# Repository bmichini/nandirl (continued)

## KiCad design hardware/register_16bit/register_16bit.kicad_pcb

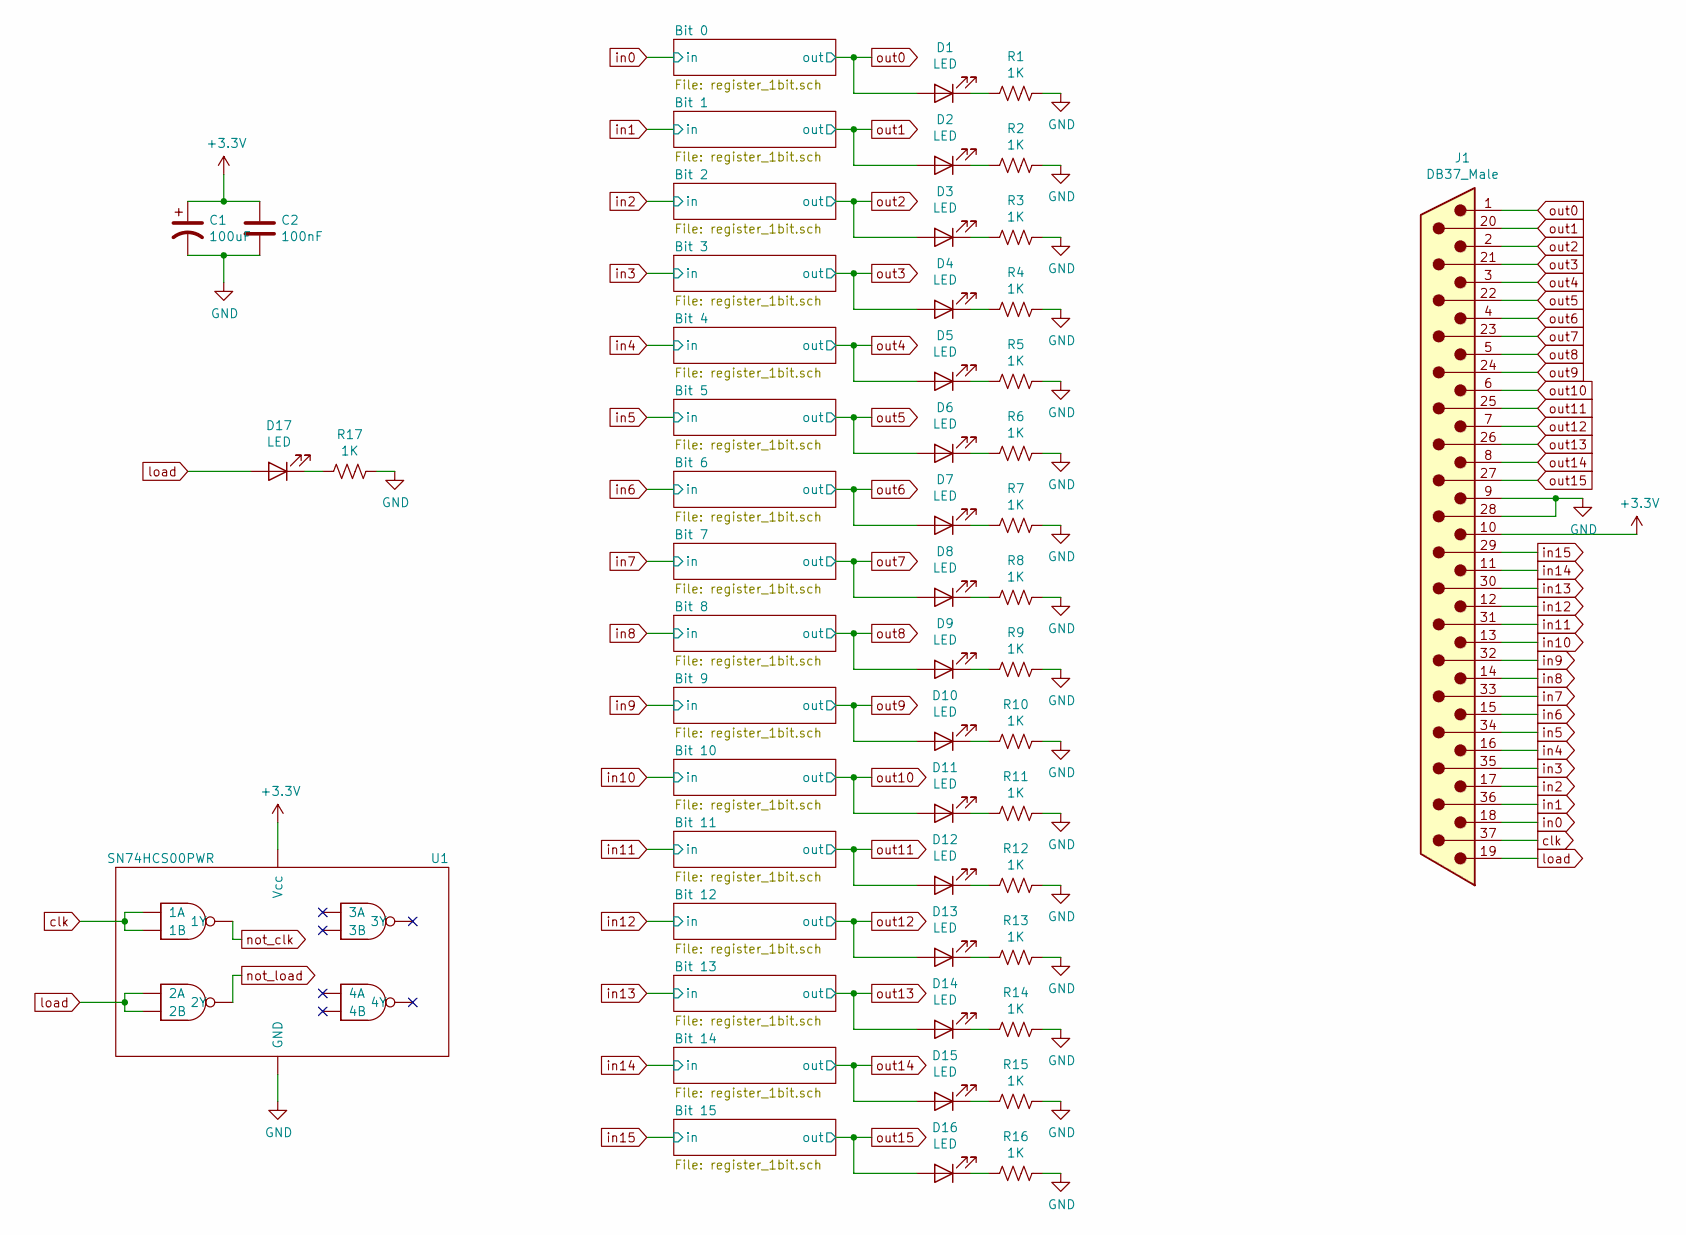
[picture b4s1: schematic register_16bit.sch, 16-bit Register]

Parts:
C1: 100uF; CP_Radial_D8.0mm_P2.50mm; Digikey PN P15797CT-ND
C2: 100nF; C_Disc_D5.0mm_W2.5mm_P5.00mm; Digikey PN BC5229CT-ND
D1, D2, D3, D4, D5, D6, D7, D8, D9, D10, D11, D12, D13, D14, D15, D16, D17: LED; LED_D5.0mm
J1: DB37_Male; DSUB-37_Male_Horizontal_P2.77x2.84mm_EdgePinOffset7.70mm_Ho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; Digikey PN AE10986-ND
R1, R2, R3, R4, R5, R6, R7, R8, R9, R10, R11, R12, R13, R14, R15, R16, R17: 1K; R_1206_3216Metric; Digikey PN P1.0KECT-ND
U1: SN74HCS00PWR; TSSOP-14_4.4x5mm_P0.65mm; Digikey PN 296-SN74HCS00PWRCT-ND

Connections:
+3V3: C1.1, C2.1, J1.10, U1.14 (Vcc); also elsewhere on the board
GND: C1.2, C2.2, J1.9, J1.28, R1.1, R2.1, R3.1, R4.1, R5.1, R6.1, R7.1, R8.1, R9.1, R10.1, R11.1, R12.1, R13.1, R14.1, R15.1, R16.1, R17.1, U1.7 (GND); also elsewhere on the board
unnamed: D1.1 (K), R1.2
unnamed: D2.1 (K), R2.2
unnamed: D3.1 (K), R3.2
unnamed: D4.1 (K), R4.2
unnamed: D5.1 (K), R5.2
unnamed: D6.1 (K), R6.2
unnamed: D7.1 (K), R7.2
unnamed: D8.1 (K), R8.2
unnamed: D9.1 (K), R9.2
unnamed: D10.1 (K), R10.2
unnamed: D11.1 (K), R11.2
unnamed: D12.1 (K), R12.2
unnamed: D13.1 (K), R13.2
unnamed: D14.1 (K), R14.2
unnamed: D15.1 (K), R15.2
unnamed: D16.1 (K), R16.2
unnamed: D17.1 (K), R17.2
clk: J1.37, U1.1 (1A), U1.2 (1B); also elsewhere on the board
in0: J1.18; also elsewhere on the board
in1: J1.36; also elsewhere on the board
in2: J1.17; also elsewhere on the board
in3: J1.35; also elsewhere on the board
in4: J1.16; also elsewhere on the board
in5: J1.34; also elsewhere on the board
in6: J1.15; also elsewhere on the board
in7: J1.33; also elsewhere on the board
in8: J1.14; also elsewhere on the board
in9: J1.32; also elsewhere on the board
in10: J1.13; also elsewhere on the board
in11: J1.31; also elsewhere on the board
in12: J1.12; also elsewhere on the board
in13: J1.30; also elsewhere on the board
in14: J1.11; also elsewhere on the board
in15: J1.29; also elsewhere on the board
load: D17.2 (A), J1.19, U1.4 (2A), U1.5 (2B); also elsewhere on the board
not_clk: U1.3 (1Y); also elsewhere on the board
not_load: U1.6 (2Y); also elsewhere on the board
out0: D1.2 (A), J1.1; also elsewhere on the board
out1: D2.2 (A), J1.20; also elsewhere on the board
out2: D3.2 (A), J1.2; also elsewhere on the board
out3: D4.2 (A), J1.21; also elsewhere on the board
out4: D5.2 (A), J1.3; also elsewhere on the board
out5: D6.2 (A), J1.22; also elsewhere on the board
out6: D7.2 (A), J1.4; also elsewhere on the board
out7: D8.2 (A), J1.23; also elsewhere on the board
out8: D9.2 (A), J1.5; also elsewhere on the board
out9: D10.2 (A), J1.24; also elsewhere on the board
out10: D11.2 (A), J1.6; also elsewhere on the board
out11: D12.2 (A), J1.25; also elsewhere on the board
out12: D13.2 (A), J1.7; also elsewhere on the board
out13: D14.2 (A), J1.26; also elsewhere on the board
out14: D15.2 (A), J1.8; also elsewhere on the board
out15: D16.2 (A), J1.27; also elsewhere on the board

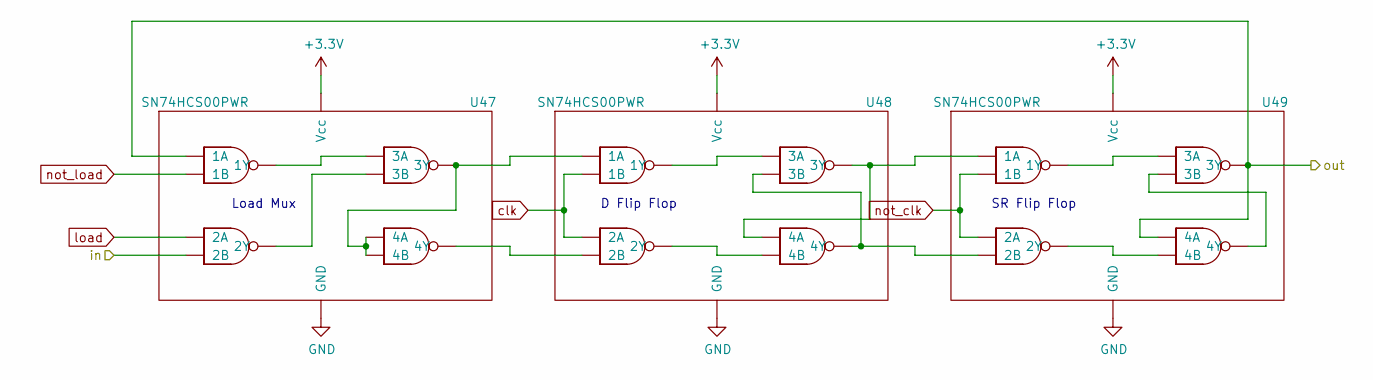
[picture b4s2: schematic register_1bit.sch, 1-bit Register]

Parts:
U47, U48, U49: SN74HCS00PWR; TSSOP-14_4.4x5mm_P0.65mm; Digikey PN 296-SN74HCS00PWRCT-ND

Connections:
+3V3: U47.14 (Vcc), U48.14 (Vcc), U49.14 (Vcc); also elsewhere on the board
GND: U47.7 (GND), U48.7 (GND), U49.7 (GND); also elsewhere on the board
unnamed: U47.3 (1Y), U47.9 (3A)
unnamed: U47.6 (2Y), U47.10 (3B)
unnamed: U47.11 (4Y), U48.5 (2B)
unnamed: U47.8 (3Y), U47.12 (4A), U47.13 (4B), U48.1 (1A)
unnamed: U48.3 (1Y), U48.9 (3A)
unnamed: U48.10 (3B), U48.11 (4Y), U49.5 (2B)
unnamed: U48.8 (3Y), U48.12 (4A), U49.1 (1A)
unnamed: U48.6 (2Y), U48.13 (4B)
unnamed: U49.3 (1Y), U49.9 (3A)
unnamed: U49.10 (3B), U49.11 (4Y)
unnamed: U49.6 (2Y), U49.13 (4B)
clk: U48.2 (1B), U48.4 (2A); also elsewhere on the board
in0: U47.5 (2B); also elsewhere on the board
load: U47.4 (2A); also elsewhere on the board
not_clk: U49.2 (1B), U49.4 (2A); also elsewhere on the board
not_load: U47.2 (1B); also elsewhere on the board
out0: U47.1 (1A), U49.8 (3Y), U49.12 (4A); also elsewhere on the board

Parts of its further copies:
U2, U3, U4, U5, U6, U7, U8, U9, U10, U11, U12, U13, U14, U15, U16, U17, U18, U19, U20, U21, U22, U23, U24, U25, U26, U27, U28, U29, U30, U31, U32, U33, U34, U35, U36, U37, U38, U39, U40, U41, U42, U43, U44, U45, U46: SN74HCS00PWR; TSSOP-14_4.4x5mm_P0.65mm; Digikey PN 296-SN74HCS00PWRCT-ND

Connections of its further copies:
+3V3: U2.14 (Vcc), U3.14 (Vcc), U4.14 (Vcc), U5.14 (Vcc), U6.14 (Vcc), U7.14 (Vcc), U8.14 (Vcc), U9.14 (Vcc), U10.14 (Vcc), U11.14 (Vcc), U12.14 (Vcc), U13.14 (Vcc), U14.14 (Vcc), U15.14 (Vcc), U16.14 (Vcc), U17.14 (Vcc), U18.14 (Vcc), U19.14 (Vcc), U20.14 (Vcc), U21.14 (Vcc), U22.14 (Vcc), U23.14 (Vcc), U24.14 (Vcc), U25.14 (Vcc), U26.14 (Vcc), U27.14 (Vcc), U28.14 (Vcc), U29.14 (Vcc), U30.14 (Vcc), U31.14 (Vcc), U32.14 (Vcc), U33.14 (Vcc), U34.14 (Vcc), U35.14 (Vcc), U36.14 (Vcc), U37.14 (Vcc), U38.14 (Vcc), U39.14 (Vcc), U40.14 (Vcc), U41.14 (Vcc), U42.14 (Vcc), U43.14 (Vcc), U44.14 (Vcc), U45.14 (Vcc), U46.14 (Vcc); also elsewhere on the board
GND: U2.7 (GND), U3.7 (GND), U4.7 (GND), U5.7 (GND), U6.7 (GND), U7.7 (GND), U8.7 (GND), U9.7 (GND), U10.7 (GND), U11.7 (GND), U12.7 (GND), U13.7 (GND), U14.7 (GND), U15.7 (GND), U16.7 (GND), U17.7 (GND), U18.7 (GND), U19.7 (GND), U20.7 (GND), U21.7 (GND), U22.7 (GND), U23.7 (GND), U24.7 (GND), U25.7 (GND), U26.7 (GND), U27.7 (GND), U28.7 (GND), U29.7 (GND), U30.7 (GND), U31.7 (GND), U32.7 (GND), U33.7 (GND), U34.7 (GND), U35.7 (GND), U36.7 (GND), U37.7 (GND), U38.7 (GND), U39.7 (GND), U40.7 (GND), U41.7 (GND), U42.7 (GND), U43.7 (GND), U44.7 (GND), U45.7 (GND), U46.7 (GND); also elsewhere on the board
unnamed: U2.3 (1Y), U2.9 (3A)
unnamed: U2.6 (2Y), U2.10 (3B)
unnamed: U2.11 (4Y), U3.5 (2B)
unnamed: U2.8 (3Y), U2.12 (4A), U2.13 (4B), U3.1 (1A)
unnamed: U3.3 (1Y), U3.9 (3A)
unnamed: U3.10 (3B), U3.11 (4Y), U4.5 (2B)
unnamed: U3.8 (3Y), U3.12 (4A), U4.1 (1A)
unnamed: U3.6 (2Y), U3.13 (4B)
unnamed: U4.3 (1Y), U4.9 (3A)
unnamed: U4.10 (3B), U4.11 (4Y)
unnamed: U4.6 (2Y), U4.13 (4B)
unnamed: U5.3 (1Y), U5.9 (3A)
unnamed: U5.6 (2Y), U5.10 (3B)
unnamed: U5.11 (4Y), U6.5 (2B)
unnamed: U5.8 (3Y), U5.12 (4A), U5.13 (4B), U6.1 (1A)
unnamed: U6.3 (1Y), U6.9 (3A)
unnamed: U6.10 (3B), U6.11 (4Y), U7.5 (2B)
unnamed: U6.8 (3Y), U6.12 (4A), U7.1 (1A)
unnamed: U6.6 (2Y), U6.13 (4B)
unnamed: U7.3 (1Y), U7.9 (3A)
unnamed: U7.10 (3B), U7.11 (4Y)
unnamed: U7.6 (2Y), U7.13 (4B)
unnamed: U8.3 (1Y), U8.9 (3A)
unnamed: U8.6 (2Y), U8.10 (3B)
unnamed: U8.11 (4Y), U9.5 (2B)
unnamed: U8.8 (3Y), U8.12 (4A), U8.13 (4B), U9.1 (1A)
unnamed: U9.3 (1Y), U9.9 (3A)
unnamed: U9.6 (2Y), U9.13 (4B)
unnamed: U9.8 (3Y), U9.12 (4A), U10.1 (1A)
unnamed: U10.3 (1Y), U10.9 (3A)
unnamed: U9.10 (3B), U9.11 (4Y), U10.5 (2B)
unnamed: U10.10 (3B), U10.11 (4Y)
unnamed: U10.6 (2Y), U10.13 (4B)
unnamed: U11.3 (1Y), U11.9 (3A)
unnamed: U11.6 (2Y), U11.10 (3B)
unnamed: U11.11 (4Y), U12.5 (2B)
unnamed: U11.8 (3Y), U11.12 (4A), U11.13 (4B), U12.1 (1A)
unnamed: U12.3 (1Y), U12.9 (3A)
unnamed: U12.10 (3B), U12.11 (4Y), U13.5 (2B)
unnamed: U12.8 (3Y), U12.12 (4A), U13.1 (1A)
unnamed: U12.6 (2Y), U12.13 (4B)
unnamed: U13.3 (1Y), U13.9 (3A)
unnamed: U13.10 (3B), U13.11 (4Y)
unnamed: U13.6 (2Y), U13.13 (4B)
unnamed: U14.3 (1Y), U14.9 (3A)
unnamed: U14.6 (2Y), U14.10 (3B)
unnamed: U14.11 (4Y), U15.5 (2B)
unnamed: U14.8 (3Y), U14.12 (4A), U14.13 (4B), U15.1 (1A)
unnamed: U15.3 (1Y), U15.9 (3A)
unnamed: U15.10 (3B), U15.11 (4Y), U16.5 (2B)
unnamed: U15.8 (3Y), U15.12 (4A), U16.1 (1A)
unnamed: U15.6 (2Y), U15.13 (4B)
unnamed: U16.3 (1Y), U16.9 (3A)
unnamed: U16.10 (3B), U16.11 (4Y)
unnamed: U16.6 (2Y), U16.13 (4B)
unnamed: U17.3 (1Y), U17.9 (3A)
unnamed: U17.6 (2Y), U17.10 (3B)
unnamed: U17.11 (4Y), U18.5 (2B)
unnamed: U17.8 (3Y), U17.12 (4A), U17.13 (4B), U18.1 (1A)
unnamed: U18.3 (1Y), U18.9 (3A)
unnamed: U18.10 (3B), U18.11 (4Y), U19.5 (2B)
unnamed: U18.8 (3Y), U18.12 (4A), U19.1 (1A)
unnamed: U18.6 (2Y), U18.13 (4B)
unnamed: U19.3 (1Y), U19.9 (3A)
unnamed: U19.10 (3B), U19.11 (4Y)
unnamed: U19.6 (2Y), U19.13 (4B)
unnamed: U20.3 (1Y), U20.9 (3A)
unnamed: U20.6 (2Y), U20.10 (3B)
unnamed: U20.11 (4Y), U21.5 (2B)
unnamed: U20.8 (3Y), U20.12 (4A), U20.13 (4B), U21.1 (1A)
unnamed: U21.3 (1Y), U21.9 (3A)
unnamed: U21.10 (3B), U21.11 (4Y), U22.5 (2B)
unnamed: U21.8 (3Y), U21.12 (4A), U22.1 (1A)
unnamed: U21.6 (2Y), U21.13 (4B)
unnamed: U22.3 (1Y), U22.9 (3A)
unnamed: U22.10 (3B), U22.11 (4Y)
unnamed: U22.6 (2Y), U22.13 (4B)
unnamed: U23.3 (1Y), U23.9 (3A)
unnamed: U23.6 (2Y), U23.10 (3B)
unnamed: U23.11 (4Y), U24.5 (2B)
unnamed: U23.8 (3Y), U23.12 (4A), U23.13 (4B), U24.1 (1A)
unnamed: U24.3 (1Y), U24.9 (3A)
unnamed: U24.10 (3B), U24.11 (4Y), U25.5 (2B)
unnamed: U24.8 (3Y), U24.12 (4A), U25.1 (1A)
unnamed: U24.6 (2Y), U24.13 (4B)
unnamed: U25.3 (1Y), U25.9 (3A)
unnamed: U25.10 (3B), U25.11 (4Y)
unnamed: U25.6 (2Y), U25.13 (4B)
unnamed: U26.3 (1Y), U26.9 (3A)
unnamed: U26.6 (2Y), U26.10 (3B)
unnamed: U26.11 (4Y), U27.5 (2B)
unnamed: U26.8 (3Y), U26.12 (4A), U26.13 (4B), U27.1 (1A)
unnamed: U27.3 (1Y), U27.9 (3A)
unnamed: U27.10 (3B), U27.11 (4Y), U28.5 (2B)
unnamed: U27.8 (3Y), U27.12 (4A), U28.1 (1A)
unnamed: U27.6 (2Y), U27.13 (4B)
unnamed: U28.3 (1Y), U28.9 (3A)
unnamed: U28.10 (3B), U28.11 (4Y)
unnamed: U28.6 (2Y), U28.13 (4B)
unnamed: U29.3 (1Y), U29.9 (3A)
unnamed: U29.6 (2Y), U29.10 (3B)
unnamed: U29.11 (4Y), U30.5 (2B)
unnamed: U29.8 (3Y), U29.12 (4A), U29.13 (4B), U30.1 (1A)
unnamed: U30.3 (1Y), U30.9 (3A)
unnamed: U30.10 (3B), U30.11 (4Y), U31.5 (2B)
unnamed: U30.8 (3Y), U30.12 (4A), U31.1 (1A)
unnamed: U30.6 (2Y), U30.13 (4B)
unnamed: U31.3 (1Y), U31.9 (3A)
unnamed: U31.10 (3B), U31.11 (4Y)
unnamed: U31.6 (2Y), U31.13 (4B)
unnamed: U32.3 (1Y), U32.9 (3A)
unnamed: U32.6 (2Y), U32.10 (3B)
unnamed: U32.11 (4Y), U33.5 (2B)
unnamed: U32.8 (3Y), U32.12 (4A), U32.13 (4B), U33.1 (1A)
unnamed: U33.3 (1Y), U33.9 (3A)
unnamed: U33.10 (3B), U33.11 (4Y), U34.5 (2B)
unnamed: U33.8 (3Y), U33.12 (4A), U34.1 (1A)
unnamed: U33.6 (2Y), U33.13 (4B)
unnamed: U34.3 (1Y), U34.9 (3A)
unnamed: U34.10 (3B), U34.11 (4Y)
unnamed: U34.6 (2Y), U34.13 (4B)
unnamed: U35.3 (1Y), U35.9 (3A)
unnamed: U35.6 (2Y), U35.10 (3B)
unnamed: U35.11 (4Y), U36.5 (2B)
unnamed: U35.8 (3Y), U35.12 (4A), U35.13 (4B), U36.1 (1A)
unnamed: U36.3 (1Y), U36.9 (3A)
unnamed: U36.10 (3B), U36.11 (4Y), U37.5 (2B)
unnamed: U36.8 (3Y), U36.12 (4A), U37.1 (1A)
unnamed: U36.6 (2Y), U36.13 (4B)
unnamed: U37.3 (1Y), U37.9 (3A)
unnamed: U37.10 (3B), U37.11 (4Y)
unnamed: U37.6 (2Y), U37.13 (4B)
unnamed: U38.3 (1Y), U38.9 (3A)
unnamed: U38.6 (2Y), U38.10 (3B)
unnamed: U38.11 (4Y), U39.5 (2B)
unnamed: U38.8 (3Y), U38.12 (4A), U38.13 (4B), U39.1 (1A)
unnamed: U39.3 (1Y), U39.9 (3A)
unnamed: U39.10 (3B), U39.11 (4Y), U40.5 (2B)
unnamed: U39.8 (3Y), U39.12 (4A), U40.1 (1A)
unnamed: U39.6 (2Y), U39.13 (4B)
unnamed: U40.3 (1Y), U40.9 (3A)
unnamed: U40.10 (3B), U40.11 (4Y)
unnamed: U40.6 (2Y), U40.13 (4B)
unnamed: U41.3 (1Y), U41.9 (3A)
unnamed: U41.6 (2Y), U41.10 (3B)
unnamed: U41.11 (4Y), U42.5 (2B)
unnamed: U41.8 (3Y), U41.12 (4A), U41.13 (4B), U42.1 (1A)
unnamed: U42.3 (1Y), U42.9 (3A)
unnamed: U42.10 (3B), U42.11 (4Y), U43.5 (2B)
unnamed: U42.8 (3Y), U42.12 (4A), U43.1 (1A)
unnamed: U42.6 (2Y), U42.13 (4B)
unnamed: U43.3 (1Y), U43.9 (3A)
unnamed: U43.10 (3B), U43.11 (4Y)
unnamed: U43.6 (2Y), U43.13 (4B)
unnamed: U44.3 (1Y), U44.9 (3A)
unnamed: U44.6 (2Y), U44.10 (3B)
unnamed: U44.11 (4Y), U45.5 (2B)
unnamed: U44.8 (3Y), U44.12 (4A), U44.13 (4B), U45.1 (1A)
unnamed: U45.3 (1Y), U45.9 (3A)
unnamed: U45.10 (3B), U45.11 (4Y), U46.5 (2B)
unnamed: U45.8 (3Y), U45.12 (4A), U46.1 (1A)
unnamed: U45.6 (2Y), U45.13 (4B)
unnamed: U46.3 (1Y), U46.9 (3A)
unnamed: U46.10 (3B), U46.11 (4Y)
unnamed: U46.6 (2Y), U46.13 (4B)
clk: U3.2 (1B), U3.4 (2A), U6.2 (1B), U6.4 (2A), U9.2 (1B), U9.4 (2A), U12.2 (1B), U12.4 (2A), U15.2 (1B), U15.4 (2A), U18.2 (1B), U18.4 (2A), U21.2 (1B), U21.4 (2A), U24.2 (1B), U24.4 (2A), U27.2 (1B), U27.4 (2A), U30.2 (1B), U30.4 (2A), U33.2 (1B), U33.4 (2A), U36.2 (1B), U36.4 (2A), U39.2 (1B), U39.4 (2A), U42.2 (1B), U42.4 (2A), U45.2 (1B), U45.4 (2A); also elsewhere on the board
in1: U2.5 (2B); also elsewhere on the board
in2: U5.5 (2B); also elsewhere on the board
in3: U8.5 (2B); also elsewhere on the board
in4: U11.5 (2B); also elsewhere on the board
in5: U14.5 (2B); also elsewhere on the board
in6: U17.5 (2B); also elsewhere on the board
in7: U20.5 (2B); also elsewhere on the board
in8: U23.5 (2B); also elsewhere on the board
in9: U26.5 (2B); also elsewhere on the board
in10: U29.5 (2B); also elsewhere on the board
in11: U32.5 (2B); also elsewhere on the board
in12: U35.5 (2B); also elsewhere on the board
in13: U38.5 (2B); also elsewhere on the board
in14: U41.5 (2B); also elsewhere on the board
in15: U44.5 (2B); also elsewhere on the board
load: U2.4 (2A), U5.4 (2A), U8.4 (2A), U11.4 (2A), U14.4 (2A), U17.4 (2A), U20.4 (2A), U23.4 (2A), U26.4 (2A), U29.4 (2A), U32.4 (2A), U35.4 (2A), U38.4 (2A), U41.4 (2A), U44.4 (2A); also elsewhere on the board
not_clk: U4.2 (1B), U4.4 (2A), U7.2 (1B), U7.4 (2A), U10.2 (1B), U10.4 (2A), U13.2 (1B), U13.4 (2A), U16.2 (1B), U16.4 (2A), U19.2 (1B), U19.4 (2A), U22.2 (1B), U22.4 (2A), U25.2 (1B), U25.4 (2A), U28.2 (1B), U28.4 (2A), U31.2 (1B), U31.4 (2A), U34.2 (1B), U34.4 (2A), U37.2 (1B), U37.4 (2A), U40.2 (1B), U40.4 (2A), U43.2 (1B), U43.4 (2A), U46.2 (1B), U46.4 (2A); also elsewhere on the board
not_load: U2.2 (1B), U5.2 (1B), U8.2 (1B), U11.2 (1B), U14.2 (1B), U17.2 (1B), U20.2 (1B), U23.2 (1B), U26.2 (1B), U29.2 (1B), U32.2 (1B), U35.2 (1B), U38.2 (1B), U41.2 (1B), U44.2 (1B); also elsewhere on the board
out1: U2.1 (1A), U4.8 (3Y), U4.12 (4A); also elsewhere on the board
out2: U5.1 (1A), U7.8 (3Y), U7.12 (4A); also elsewhere on the board
out3: U8.1 (1A), U10.8 (3Y), U10.12 (4A); also elsewhere on the board
out4: U11.1 (1A), U13.8 (3Y), U13.12 (4A); also elsewhere on the board
out5: U14.1 (1A), U16.8 (3Y), U16.12 (4A); also elsewhere on the board
out6: U17.1 (1A), U19.8 (3Y), U19.12 (4A); also elsewhere on the board
out7: U20.1 (1A), U22.8 (3Y), U22.12 (4A); also elsewhere on the board
out8: U23.1 (1A), U25.8 (3Y), U25.12 (4A); also elsewhere on the board
out9: U26.1 (1A), U28.8 (3Y), U28.12 (4A); also elsewhere on the board
out10: U29.1 (1A), U31.8 (3Y), U31.12 (4A); also elsewhere on the board
out11: U32.1 (1A), U34.8 (3Y), U34.12 (4A); also elsewhere on the board
out12: U35.1 (1A), U37.8 (3Y), U37.12 (4A); also elsewhere on the board
out13: U38.1 (1A), U40.8 (3Y), U40.12 (4A); also elsewhere on the board
out14: U41.1 (1A), U43.8 (3Y), U43.12 (4A); also elsewhere on the board
out15: U44.1 (1A), U46.8 (3Y), U46.12 (4A); also elsewhere on the board

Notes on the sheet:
Load Mux
D Flip Flop
SR Flip Flop

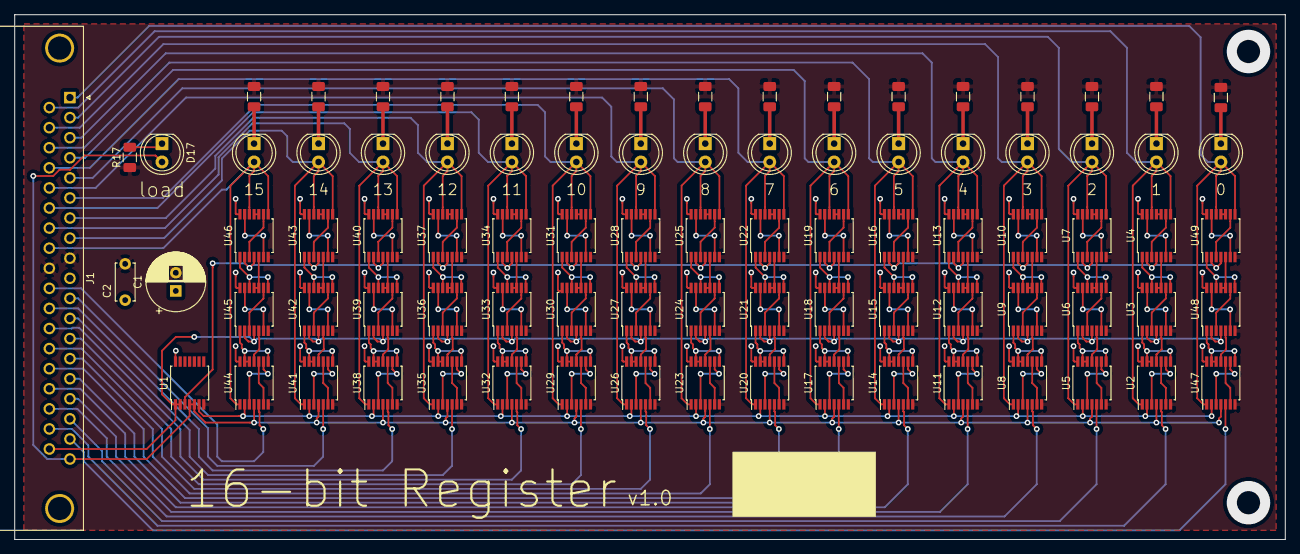
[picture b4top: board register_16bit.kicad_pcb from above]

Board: 2 copper layers, 175.3 x 72.4 mm, 86 parts (0 on the bottom side), 231 nets.

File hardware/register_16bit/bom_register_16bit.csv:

Reference, Quantity, Value, Footprint, Datasheet, Digikey PN
C1 ,1,"100uF","Capacitor_THT:CP_Radial_D8.0mm_P2.50mm","~","P15797CT-ND"
C2 ,1,"100nF","Capacitor_THT:C_Disc_D5.0mm_W2.5mm_P5.00mm","~","BC5229CT-ND"
D1 D2 D3 D4 D5 D6 D7 D8 D9 D10 D11 D12 D13 D14 D15 D16 D17 ,17,"LED","LED_THT:LED_D5.0mm","~"
J1 ,1,"DB37_Male","Connector_Dsub:DSUB-37_Male_Horizontal_P2.77x2.84mm_EdgePinOffset7.70mm_Housed_MountingHolesOffset9.12mm"," ~","AE10986-ND"
R1 R17 R2 R3 R4 R5 R6 R7 R8 R9 R10 R11 R12 R13 R14 R15 R16 ,17,"1K","Resistor_SMD:R_1206_3216Metric","~","P1.0KECT-ND"
U1 U2 U3 U4 U5 U6 U7 U8 U9 U10 U11 U12 U13 U14 U15 U16 U17 U18 U19 U20 U21 U22 U23 U24 U25 U26 U27 U28 U29 U30 U31 U32 U33 U34 U35 U36 U37 U38 U39 U40 U41 U42 U43 U44 U45 U46 U47 U48 U49 ,49,"SN74HCS00PWR","Package_SO:TSSOP-14_4.4x5mm_P0.65mm","","296-SN74HCS00PWRCT-ND"

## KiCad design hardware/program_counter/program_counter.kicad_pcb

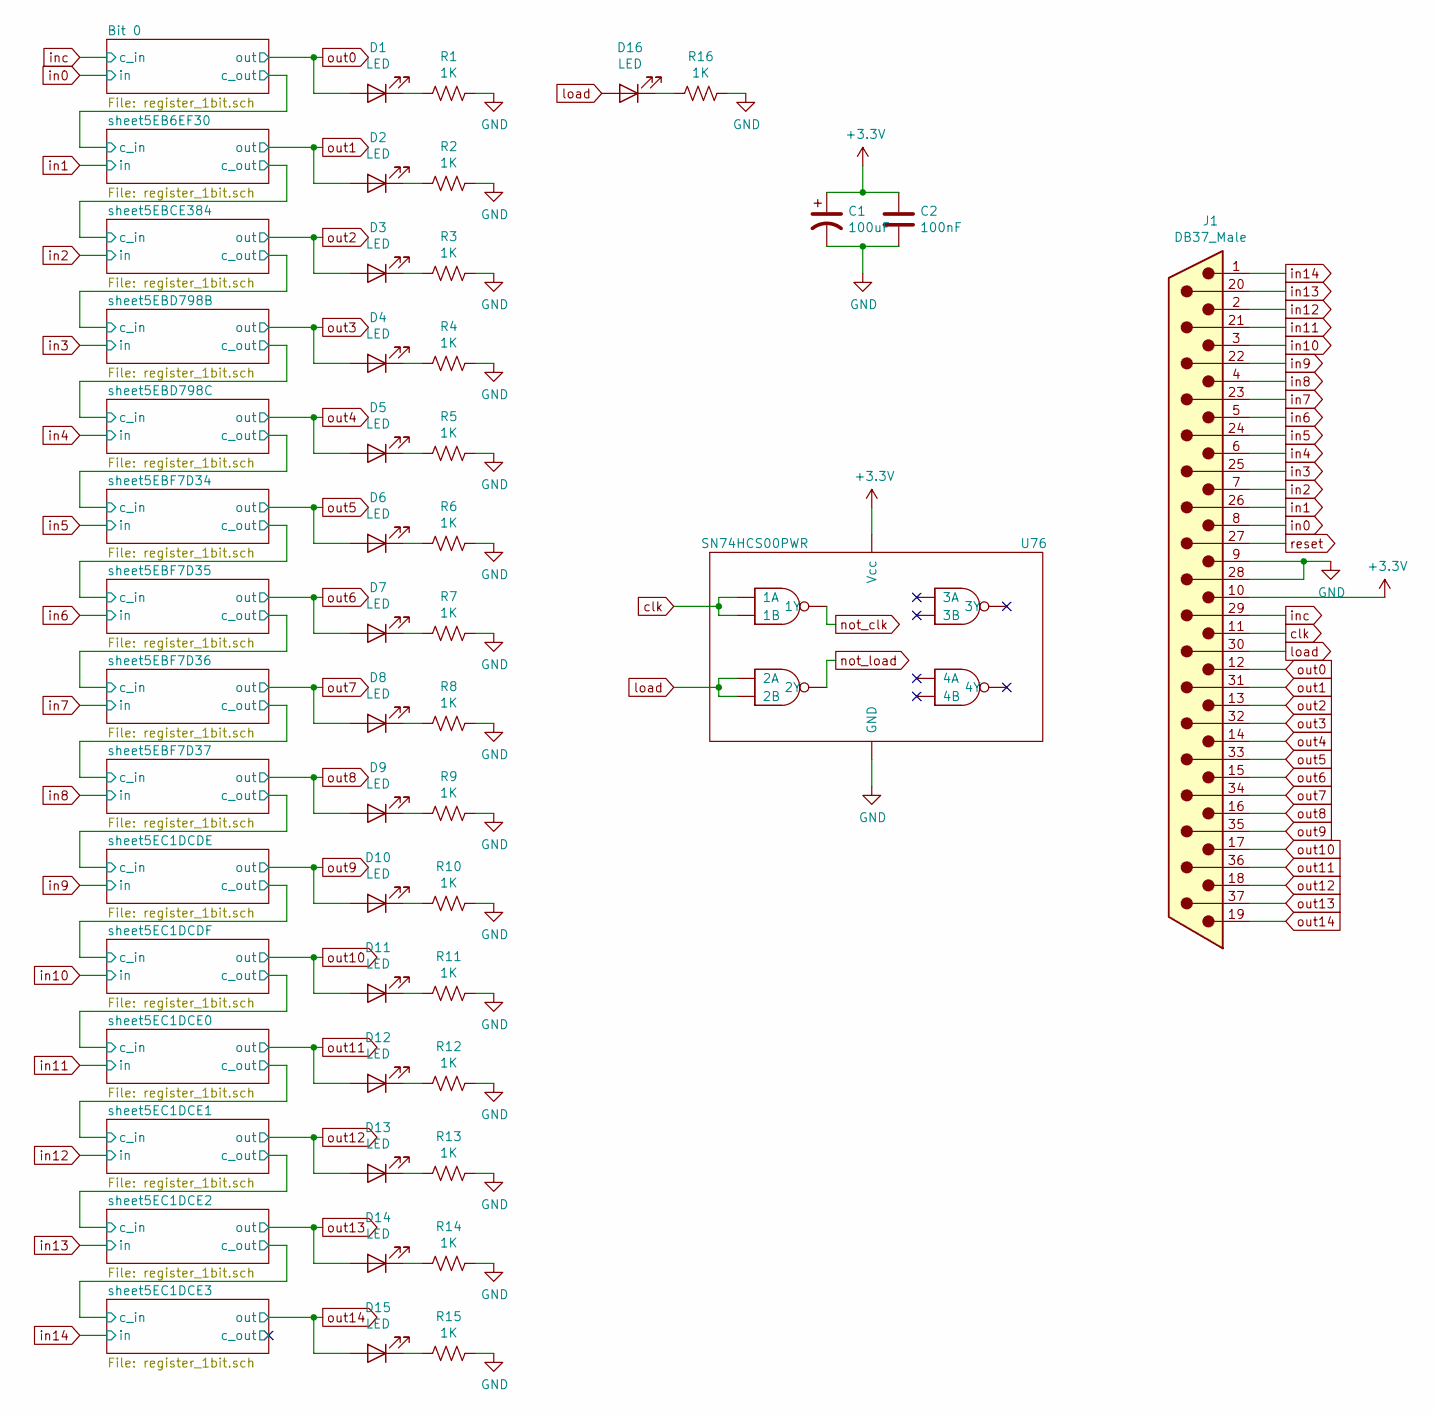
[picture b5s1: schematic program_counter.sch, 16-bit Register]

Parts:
C1: 100uF; CP_Radial_D8.0mm_P2.50mm; Digikey PN P15797CT-ND
C2: 100nF; C_Disc_D5.0mm_W2.5mm_P5.00mm; Digikey PN BC5229CT-ND
D1, D2, D3, D4, D5, D6, D7, D8, D9, D10, D11, D12, D13, D14, D15, D16: LED; LED_D5.0mm
J1: DB37_Male; DSUB-37_Male_Horizontal_P2.77x2.84mm_EdgePinOffset7.70mm_Ho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; Digikey PN AE10986-ND
R1, R2, R3, R4, R5, R6, R7, R8, R9, R10, R11, R12, R13, R14, R15, R16: 1K; R_1206_3216Metric; Digikey PN P1.0KECT-ND
U76: SN74HCS00PWR; TSSOP-14_4.4x5mm_P0.65mm; Digikey PN 296-SN74HCS00PWRCT-ND

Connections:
GND: C1.2, C2.2, J1.9, J1.28, R1.1, R2.1, R3.1, R4.1, R5.1, R6.1, R7.1, R8.1, R9.1, R10.1, R11.1, R12.1, R13.1, R14.1, R15.1, R16.1, U76.7 (GND); also elsewhere on the board
unnamed: D1.1 (K), R1.2
unnamed: D2.1 (K), R2.2
unnamed: D3.1 (K), R3.2
unnamed: D4.1 (K), R4.2
unnamed: D5.1 (K), R5.2
unnamed: D6.1 (K), R6.2
unnamed: D7.1 (K), R7.2
unnamed: D8.1 (K), R8.2
unnamed: D9.1 (K), R9.2
unnamed: D10.1 (K), R10.2
unnamed: D11.1 (K), R11.2
unnamed: D12.1 (K), R12.2
unnamed: D13.1 (K), R13.2
unnamed: D14.1 (K), R14.2
unnamed: D15.1 (K), R15.2
unnamed: D16.1 (K), R16.2
clk: J1.11, U76.1 (1A), U76.2 (1B); also elsewhere on the board
in0: J1.8; also elsewhere on the board
in1: J1.26; also elsewhere on the board
in2: J1.7; also elsewhere on the board
in3: J1.25; also elsewhere on the board
in4: J1.6; also elsewhere on the board
in5: J1.24; also elsewhere on the board
in6: J1.5; also elsewhere on the board
in7: J1.23; also elsewhere on the board
in8: J1.4; also elsewhere on the board
in9: J1.22; also elsewhere on the board
in10: J1.3; also elsewhere on the board
in11: J1.21; also elsewhere on the board
in12: J1.2; also elsewhere on the board
in13: J1.20; also elsewhere on the board
in14: J1.1; also elsewhere on the board
inc: J1.29; also elsewhere on the board
load: D16.2 (A), J1.30, U76.4 (2A), U76.5 (2B); also elsewhere on the board
not_clk: U76.3 (1Y); also elsewhere on the board
not_load: U76.6 (2Y); also elsewhere on the board
out0: D1.2 (A), J1.12; also elsewhere on the board
out1: D2.2 (A), J1.31; also elsewhere on the board
out2: D3.2 (A), J1.13; also elsewhere on the board
out3: D4.2 (A), J1.32; also elsewhere on the board
out4: D5.2 (A), J1.14; also elsewhere on the board
out5: D6.2 (A), J1.33; also elsewhere on the board
out6: D7.2 (A), J1.15; also elsewhere on the board
out7: D8.2 (A), J1.34; also elsewhere on the board
out8: D9.2 (A), J1.16; also elsewhere on the board
out9: D10.2 (A), J1.35; also elsewhere on the board
out10: D11.2 (A), J1.17; also elsewhere on the board
out11: D12.2 (A), J1.36; also elsewhere on the board
out12: D13.2 (A), J1.18; also elsewhere on the board
out13: D14.2 (A), J1.37; also elsewhere on the board
out14: D15.2 (A), J1.19; also elsewhere on the board
reset: J1.27; also elsewhere on the board
